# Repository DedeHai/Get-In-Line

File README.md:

# Get In Line - line-following robot
Simple line following robot using a single break-away PCB design. Using mostly 0805-components to make it easier to solder by hand. Four potentiometers at the bottom let you change the speed and regulator settings without re-programming the microcontroller. 
More information available at https://bashtelorofscience.wordpress.com/ 

License:
Software under MIT license
Hardware under Creative Commons 4.0 license: CC-BY-NC-SA

# Software
The PCB was designed in **eagle** version 7.5.0. The firmware project was created using **System Workbench for STM32** and **STM32CubeMX**.

# Fotos

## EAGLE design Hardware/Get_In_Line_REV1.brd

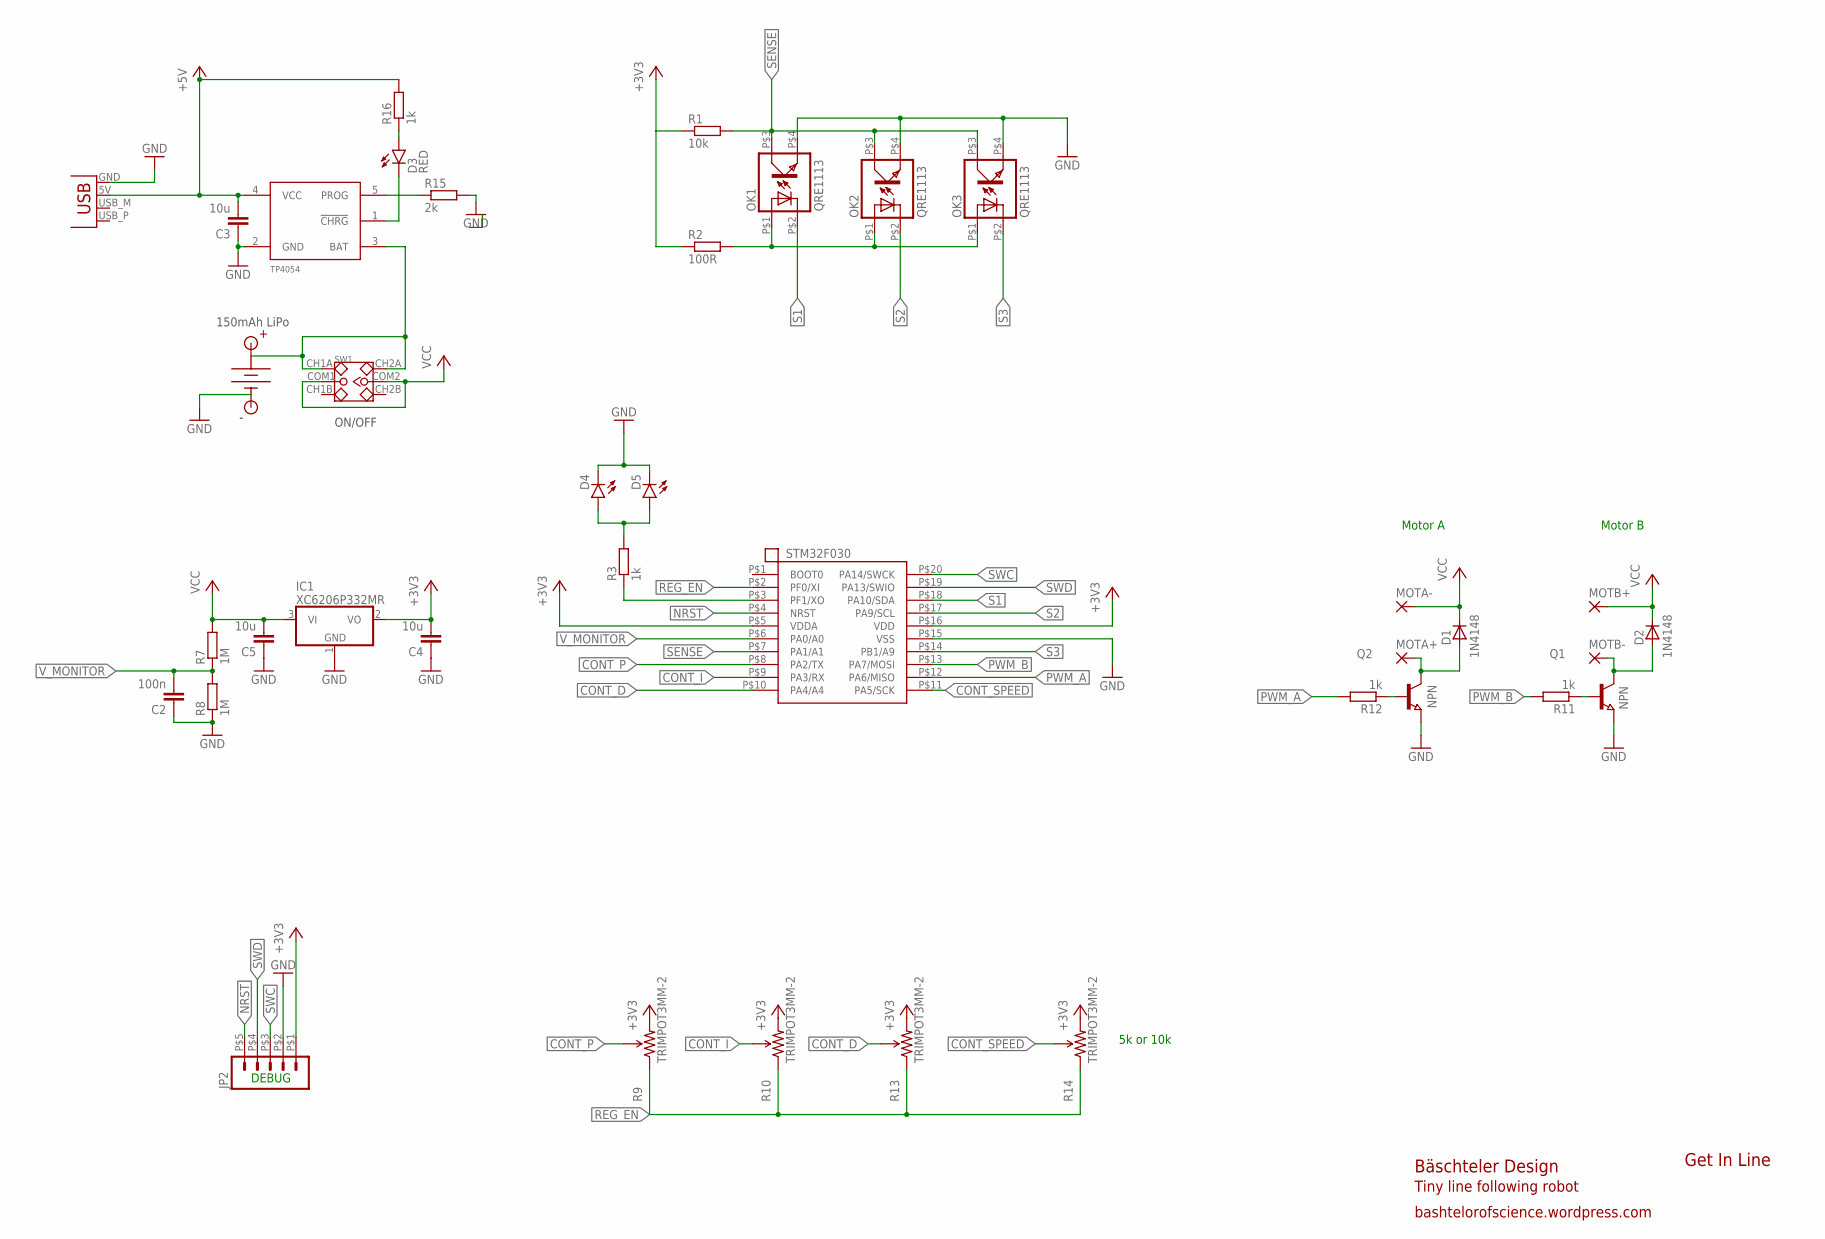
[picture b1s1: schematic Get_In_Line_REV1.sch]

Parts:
C2: 100n; C0805
C3, C4, C5: 10u; C0805
D1, D2: D-SOD-80; SOD80
D3: RED; LED-1206
D4, D5: GREEN; LED-1206
IC1: MCP1703CB; SOT23
JP1: USBPCB; USB-A-PCB
JP2: M05; SMD_HEADER_5P
MCU: STM32F030F4P6; TSSOP-20
MOTA+: 1,6/0,9
MOTA-: 1,6/0,9
MOTB+: 1,6/0,9
MOTB-: 1,6/0,9
OK1, OK2, OK3: QRE1113; DIL04
Q1, Q2: NPN-TRANSISTOR_SOT23; SOT23
R1: 10k; R0805
R2: 100R; R0805
R3, R11, R12, R16: 1k; R0805
R7, R8: 1M; R0805
R9, R10, R13, R14: TRIMPOT3MM-2; TRIMPOT-3MM-2
R15: 2k; R0805
SW1: DIP-TOGGLE-SWITCH-2CH-(2X3P-2.54); SW6-2.54-9.0X3.5X3.2+2.0MM
U$1: TP4054_LIPO_CHARGER; SOT23-5
U$5: BATTERY_PAD+1.5MM; LIPO_BATTERY_PADS_1.5MM
U$6: BATTERY_PAD-1.5MM; LIPO_BATTERY_PADS_1.5MM

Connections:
+3V3: C4.2, IC1.2 (VO), JP2.P$1 (1), MCU.P$5 (VDDA), MCU.P$16 (VDD), R1.1, R2.1, R9.3 (CW), R10.3 (CW), R13.3 (CW), R14.3 (CW)
+5V: C3.2, JP1.5V (VBUS), R16.2, U$1.4 (VCC)
CONT_D: MCU.P$10 (PA4/A4), R13.2 (WIPER)
CONT_I: MCU.P$9 (PA3/RX), R10.2 (WIPER)
CONT_P: MCU.P$8 (PA2/TX), R9.2 (WIPER)
CONT_SPEED: MCU.P$11 (PA5/SCK), R14.2 (WIPER)
GND: C2.1, C3.1, C4.1, C5.1, D4.C, D5.C, IC1.1 (GND), JP1.GND, JP2.P$2 (2), MCU.P$15 (VSS), OK1.P$4 (EMIT), OK2.P$4 (EMIT), OK3.P$4 (EMIT), Q1.2 (E), Q2.2 (E), R8.1, R15.2, U$1.2 (GND), U$6.P$1
LED: MCU.P$3 (PF1/XO), R3.1
LEDOUT: D4.A, D5.A, R3.2
unnamed: OK1.P$1 (A), OK2.P$1 (A), OK3.P$1 (A), R2.2
unnamed: R15.1, U$1.5 (PROG)
unnamed: D3.C, U$1.1 (!CHRG)
unnamed: D3.A, R16.1
unnamed: Q1.1 (B), R11.1
unnamed: Q2.1 (B), R12.1
unnamed: D1.2 (A), MOTA+.1, Q2.3 (C)
unnamed: D2.2 (A), MOTB-.1, Q1.3 (C)
NRST: JP2.P$5 (5), MCU.P$4 (NRST)
PWM_A: MCU.P$12 (PA6/MISO), R12.2
PWM_B: MCU.P$13 (PA7/MOSI), R11.2
REG_EN: MCU.P$2 (PF0/XI), R9.1 (CCW), R10.1 (CCW), R13.1 (CCW), R14.1 (CCW)
S1: MCU.P$18 (PA10/SDA), OK1.P$2 (C)
S2: MCU.P$17 (PA9/SCL), OK2.P$2 (C)
S3: MCU.P$14 (PB1/A9), OK3.P$2 (C)
SENSE: MCU.P$7 (PA1/A1), OK1.P$3 (COL), OK2.P$3 (COL), OK3.P$3 (COL), R1.2
SWC: JP2.P$3 (3), MCU.P$20 (PA14/SWCK)
SWD: JP2.P$4 (4), MCU.P$19 (PA13/SWIO)
VBAT: SW1.CH1A, SW1.CH2A, U$1.3 (BAT), U$5.P$1
VCC: C5.2, D1.1 (C), D2.1 (C), IC1.3 (VI), MOTA-.1, MOTB+.1, R7.2, SW1.COM1, SW1.COM2
V_MONITOR: C2.2, MCU.P$6 (PA0/A0), R7.1, R8.2

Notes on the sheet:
Motor A
Motor B
1N4148
XC6206P332MR
DEBUG
ON/OFF
5k or 10k
Get In Line
Bäschteler Design
bashtelorofscience.wordpress.com
Tiny line following robot
STM32F030
NPN
150mAh LiPo

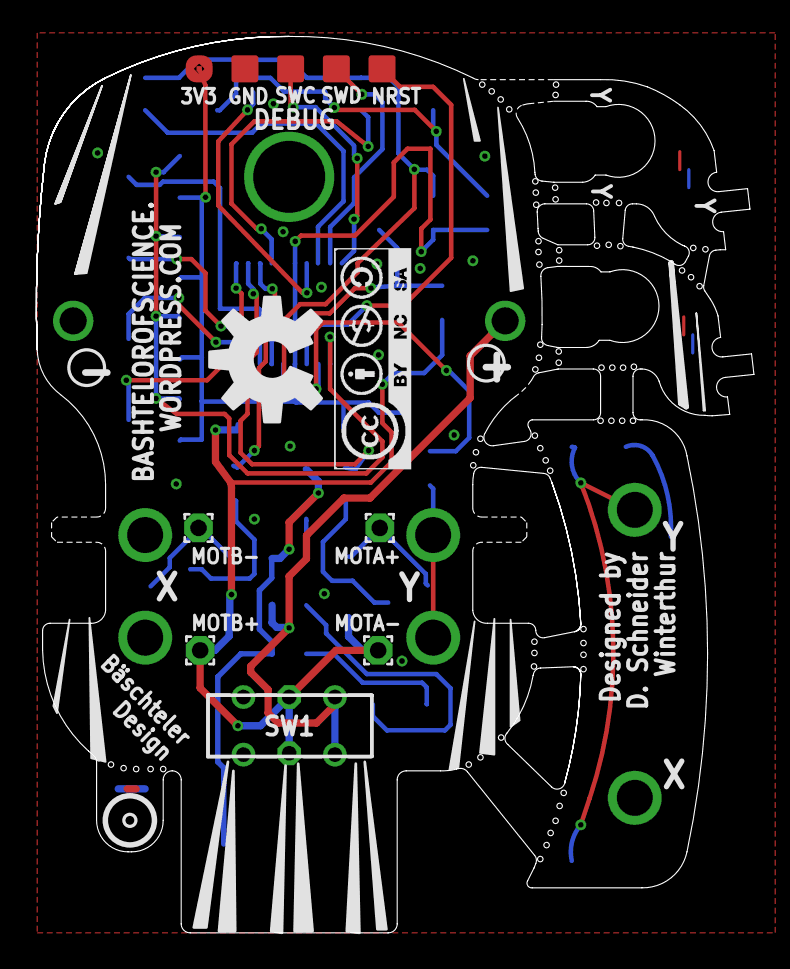
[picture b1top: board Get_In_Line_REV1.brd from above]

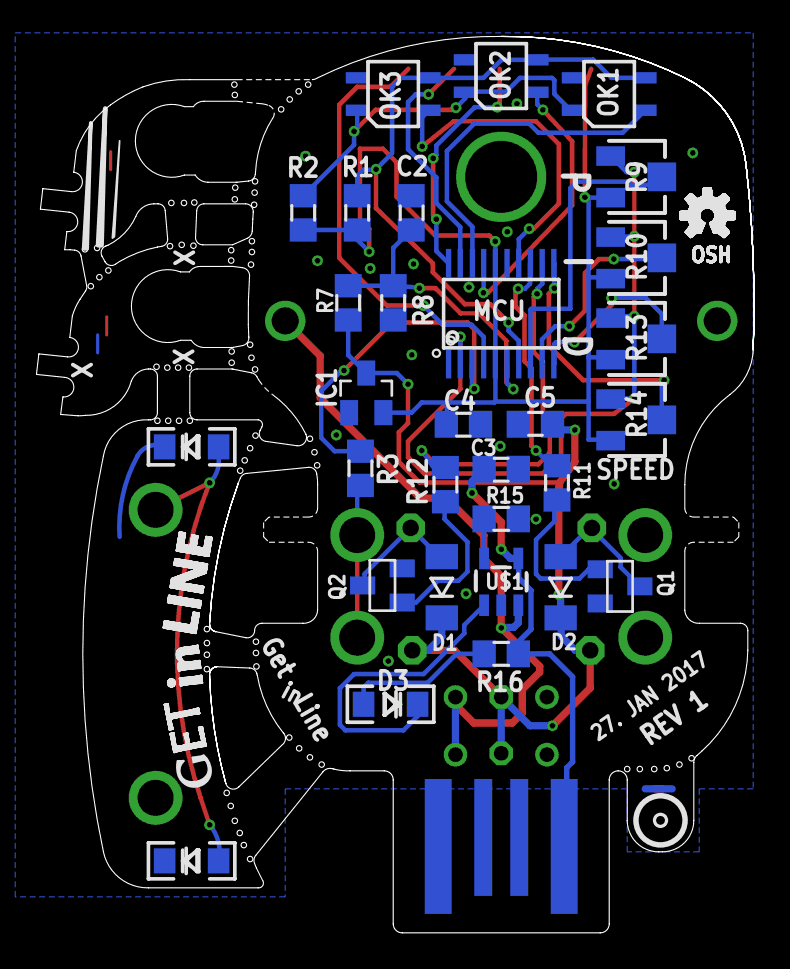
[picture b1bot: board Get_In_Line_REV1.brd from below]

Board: 2 copper layers, 39.9 x 49.8 mm, 49 parts (39 on the bottom side), 30 nets.

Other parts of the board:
U$2, U$8, U$9, U$10, U$13, U$14, U$15, U$16: OSHW-LOGO-S
U$4: CC-BY-NC-SA
U$33: OSHW-LOGO-L

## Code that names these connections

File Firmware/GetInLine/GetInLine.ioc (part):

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Mcu.Name=STM32F030F4Px
Mcu.Package=TSSOP20
Mcu.UserName=STM32F030F4Px
PA0.Mode=IN0
PA0.Signal=ADC_IN0
PA1.Mode=IN1
PA1.Signal=ADC_IN1
PA10.GPIOParameters=GPIO_Speed,PinState,GPIO_ModeDefaultOutputPP
PA10.GPIO_ModeDefaultOutputPP=GPIO_MODE_OUTPUT_PP
PA10.GPIO_Speed=GPIO_SPEED_FREQ_HIGH
PA10.PinState=GPIO_PIN_SET
PA10.Signal=GPIO_Output
PA13.Mode=Serial_Wire
PA13.Signal=SYS_SWDIO
PA14.Mode=Serial_Wire
PA14.Signal=SYS_SWCLK
PA2.Mode=IN2
PA2.Signal=ADC_IN2
PA3.Mode=IN3
PA3.Signal=ADC_IN3
PA4.Mode=IN4
PA4.Signal=ADC_IN4
PA5.Mode=IN5
PA5.Signal=ADC_IN5
PA6.GPIOParameters=GPIO_Speed
PA6.GPIO_Speed=GPIO_SPEED_FREQ_MEDIUM
PA6.Signal=S_TIM3_CH1
PA7.GPIOParameters=GPIO_Speed
PA7.GPIO_Speed=GPIO_SPEED_FREQ_MEDIUM
PA7.Signal=S_TIM3_CH2
PA9.GPIOParameters=GPIO_Speed,PinState,GPIO_ModeDefaultOutputPP
PA9.GPIO_ModeDefaultOutputPP=GPIO_MODE_OUTPUT_PP
PA9.GPIO_Speed=GPIO_SPEED_FREQ_HIGH
PA9.PinState=GPIO_PIN_SET
PA9.Signal=GPIO_Output
PB1.GPIOParameters=GPIO_Speed,PinState,GPIO_ModeDefaultOutputPP
PB1.GPIO_ModeDefaultOutputPP=GPIO_MODE_OUTPUT_PP
PB1.GPIO_Speed=GPIO_SPEED_FREQ_HIGH
PB1.PinState=GPIO_PIN_SET
PB1.Signal=GPIO_Output
PF0-OSC_IN.Signal=GPIO_Output
PF1-OSC_OUT.Signal=GPIO_Output
board=GetInLine

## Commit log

2017-01-28 :confetti_ball: Added .gitattributes & .gitignore files
2017-01-28 Initial commit
    initial commit of repository
2017-05-21 minor fix
2017-05-21 regulator improvements
    improved the regulator and added sensor self-calibration so the code
    runs well on all robots, not just the first prorotype.
2017-05-21 readme updated
2017-05-21 bauanleitung hinzugefügt

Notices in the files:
parts and their libraries:
SparkFun-Connectors: Licensing: Creative Commons ShareAlike 4.0 International - https://creativecommons.org/licenses/by-sa/4.0
